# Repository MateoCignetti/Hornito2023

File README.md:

## Trabajo práctico final de Técnicas Digitales III y Medidas Electrónicas II. UTN FR San Francisco

En este repositorio se encuentran subidos todos los archivos relacionados al trabajo práctico final las materias Técnicas Digitales III y Medidas Electrónicas II. Contiene archivos de programación de los microcontroladores, esquemáticos del circuito y de pcb, y recursos varios.

## Autores

- [ ] Alesandria, Alejo
- [ ] Cignetti, Mateo
- [ ] Delfino, Ramiro
- [ ] Galliano, Ignacio
- [ ] Rinaudo, Facundo
- [ ] Rodriguez, Manuel

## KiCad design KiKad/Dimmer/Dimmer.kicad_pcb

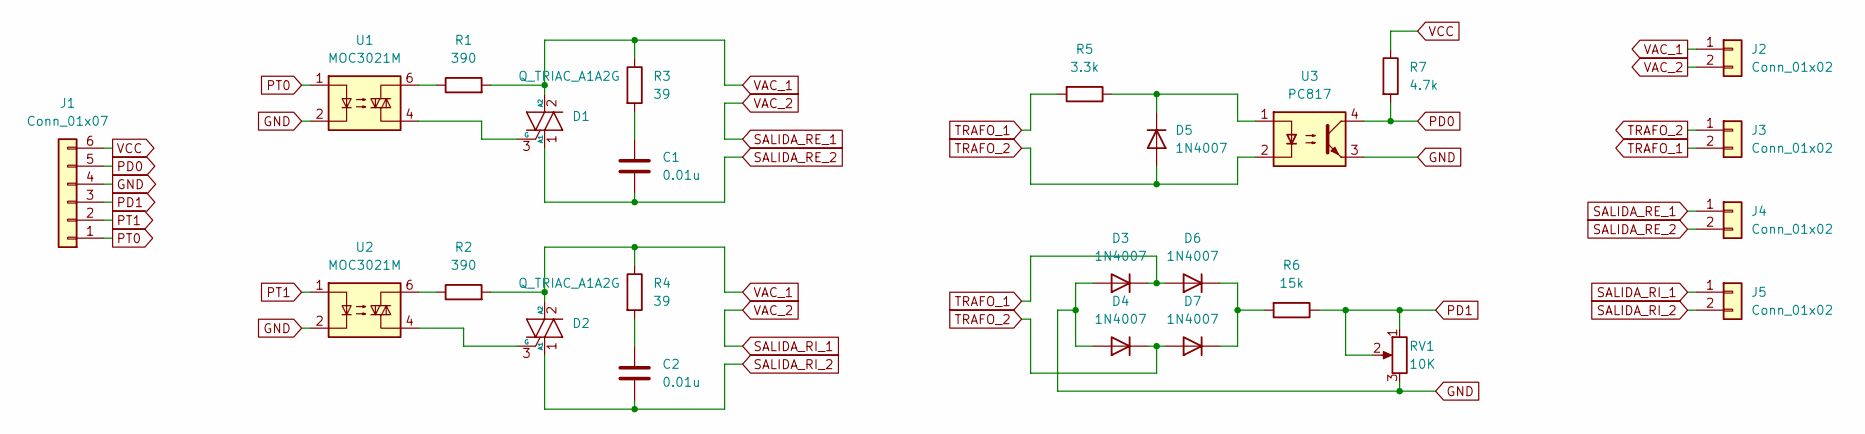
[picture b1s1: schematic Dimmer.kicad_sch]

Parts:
C1, C2: 0.01u; C_Axial_L5.1mm_D3.1mm_P10.00mm_Horizontal
D1, D2: Q_TRIAC_A1A2G; TO-220-3_Vertical
D3, D4, D5, D6, D7: 1N4007; D_DO-41_SOD81_P10.16mm_Horizontal
J1: Conn_01x07; PinHeader_1x06_P2.54mm_Vertical
J2, J3, J4, J5: Conn_01x02; TerminalBlock_bornier-2_P5.08mm
R1, R2: 390; R_Axial_DIN0207_L6.3mm_D2.5mm_P10.16mm_Horizontal
R3, R4: 39; R_Axial_DIN0207_L6.3mm_D2.5mm_P10.16mm_Horizontal
R5: 3.3k; R_Axial_DIN0207_L6.3mm_D2.5mm_P10.16mm_Horizontal
R6: 15k; R_Axial_DIN0207_L6.3mm_D2.5mm_P10.16mm_Horizontal
R7: 4.7k; R_Axial_DIN0207_L6.3mm_D2.5mm_P10.16mm_Horizontal
RV1: 10K; Potentiometer_Bourns_3296W_Vertical
U1, U2: MOC3021M; DIP-6_W7.62mm_LongPads
U3: PC817; DIP-4_W7.62mm_LongPads

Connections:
GND: D3.2 (A), D4.2 (A), J1.4, RV1.3, U1.2, U2.2, U3.3
unnamed: C1.1, R3.2
unnamed: C2.1, R4.2
unnamed: D1.3 (G), U1.4
unnamed: D2.3 (G), U2.4
unnamed: D5.1 (K), R5.1, U3.1
unnamed: D6.1 (K), D7.1 (K), R6.2
unnamed: R1.1, U1.6
unnamed: R2.1, U2.6
PD0: J1.5, R7.2, U3.4
PD1: J1.3, R6.1, RV1.1, RV1.2
PT0: J1.1, U1.1
PT1: J1.2, U2.1
SALIDA_RE_1: J2.2, J4.1, J5.1
SALIDA_RE_2: C1.2, D1.1 (A1), J4.2
SALIDA_RI_2: C2.2, D2.1 (A1), J5.2
TRAFO_1: D3.1 (K), D6.2 (A), J3.2, R5.2
TRAFO_2: D4.1 (K), D5.2 (A), D7.2 (A), J3.1, U3.2
VAC_1: D1.2 (A2), D2.2 (A2), J2.1, R1.2, R2.2, R3.1, R4.1
VCC: J1.6, R7.1

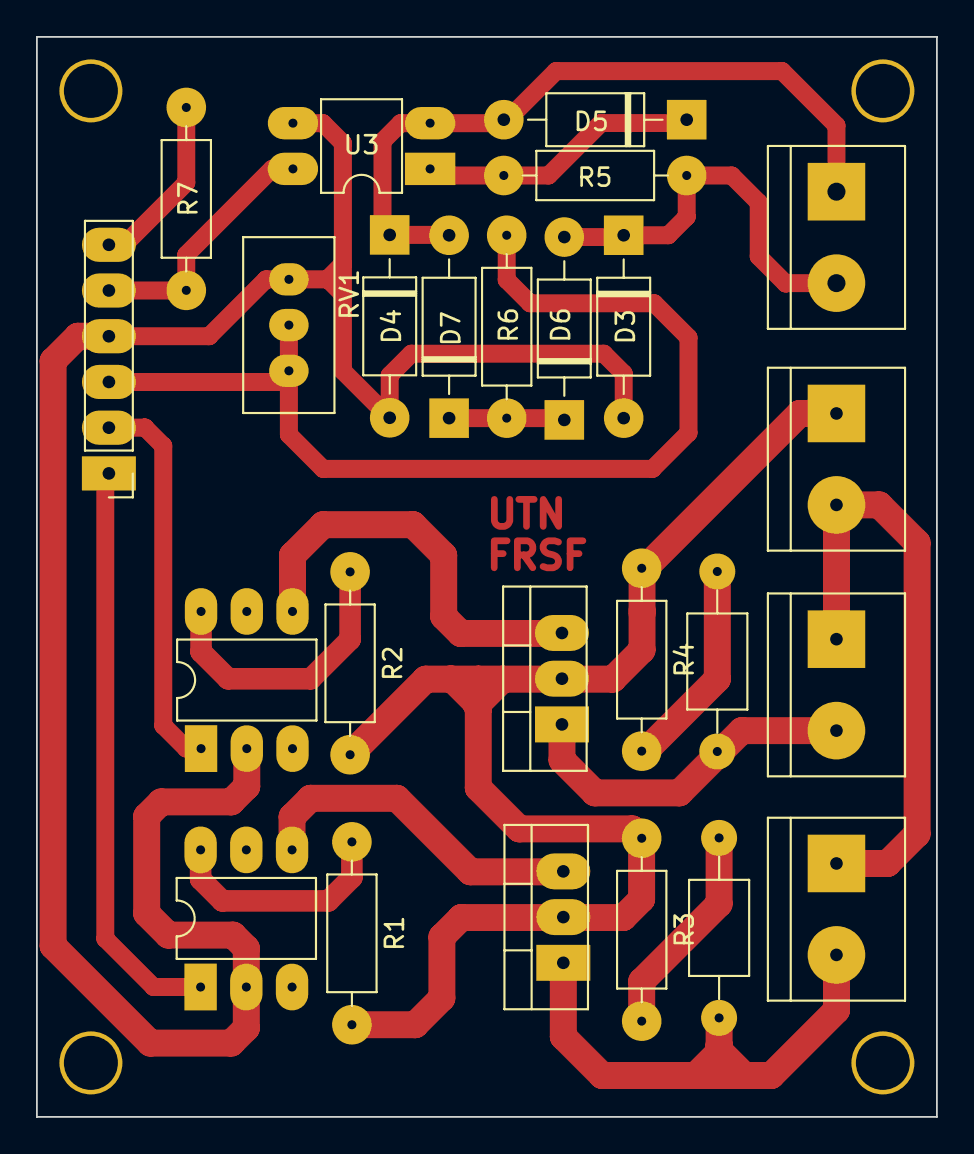
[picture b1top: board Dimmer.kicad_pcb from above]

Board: 2 copper layers, 50.0 x 60.0 mm, 25 parts (0 on the bottom side), 20 nets.

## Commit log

2023-05-18 Modificar gitignore
2023-05-18 Agregar programa test adc
2023-06-09 Agregar código test del dimmer
2023-06-13 Finalizar código de test de dimmer
2023-08-01 Agregar funcionalidad de medición de resistencia y dimmer mediante archivos .c y .h, no funciona todavía la funcionalidad del dimmer
2023-08-03 Solucionar funcionamiento del dimmer, agregar medición de temperatura con NTC
2023-09-01 Agregar test wifi y http webserver, realizado en conjunto con Manu
2023-09-18 Organizar repo y agregar recursos
2023-09-19 Agregar carpeta y diagrama de flujo de sistema de refrigeracion en conjunto con Facu
2023-09-19 Agregar test de tiempo
2023-09-25 Agregar idea del html, en conjunto con Manu
2023-09-26 Modificacion de diagrama de flujo y agregado de programa de control
2023-09-26 Probar filtro MAV para medicion de temperatura
2023-09-26 Modificar http-test para implementar carga de EPOCH, en conjunto con Manu
2023-09-29 Agregar pinout correcto, remover el otro
2023-09-29 Agregar código test de adc para plottear la señal de entrada al adc
2023-10-03 Solucionar redireccionamiento luego de presionar el botón
2023-10-03 Implementación de tabla con agregado de filas por html
2023-10-13 Diseño PCB Dimmer
2023-10-13 Fix #4
2023-10-13 Cambiar nombre de carpeta Código a Codigo para evitar problemas
2023-10-13 Agregar comentarios en http-test
2023-10-13 Rediseñar completamente el driver adc
2023-10-13 Agregar más comentarios a http-test
2023-10-18 Añadir recursos linealización de NTC
2023-10-18 Añadir informe anteproyecto
2023-10-20 Mover funcionalidad del ntc del adc.c/h a ntc.c/h
2023-10-21 Método rudimentario para agregar datos a la tabla de un ntc y tiempo actual
2023-10-24 Agregar código de prueba peltier
2023-10-24 Actualizar codigo peltier segun nueva libreria
2023-10-24 Agregar función de obtención de tensión de adc sin multisampling, arreglos varios y fix de #5
2023-10-27 Implementar #6
2023-10-29 Arreglar tarea de debugging con el nuevo driver, crear task.c/.h para manejar la creación de tareas de FreeRTOS
2023-10-30 Agregar versión inicial medición tensión rms
2023-11-03 Agregar hoja de datos del NTC de 100k
2023-11-03 Version final test-peltier
2023-11-03 Medidor de tensión RMS funcionando
2023-11-07 Agregar tarea para actualización de datos. Incluir botón de inicio
2023-11-07 Agregar sistema de control simple para potencia
2023-11-10 Subir espA con dimmer
2023-11-10 Agregar código vrms en fase, no funcional por lentitud de la tarea
2023-11-10 Agregar código vrms en fase, funcional
2023-11-10 Arreglar sistema de control de alejo, agregar mejoras en la interrupción
2023-11-10 Agregar botón de guardado y finalización
2023-11-10 Terminar sistema de control
2023-11-10 Implementar semáforo y tarea para cuando el webserver lo pida
2023-11-10 Agregar archivo excel
2023-11-13 Agregar webserver.c y sincronización con power.c
2023-11-13 Terminar sistema control, agregar Queue y semph
2023-11-13 Acomodar y comentar código de medición de potencia
2023-11-13 Arreglar fórmula de potencia
2023-11-13 Agregar envio steps a power.c
2023-11-14 Agregar sincronización para actualización de datos
2023-11-14 Agregar comunicación con tarea de sistema de control, modificaciones varias
2023-11-14 Corregir control system
2023-11-14 Actuallizar control_system.c
2023-11-14 Agregar comunicación entre tareas y mejora del sistema de control
2023-11-14 Corregir errores varios del sistema de control de placa fría
2023-11-14 Modificar Hornito-ESPA
2023-11-14 Modificar excel
2023-11-14 Cambiar imagen del pinout del devkit
2023-11-14 Corregir Hornito-ESPA
2023-11-14 Agregar monitor control_system.c
2023-11-14 Agregar versión inicial excel de tareas
2023-11-14 Agregar tarea monitoreo
2023-11-14 Arreglar creación de mutex y queues según existencia anterior
2023-11-14 Agregar sección critica en el timer y modificar delay de potencia
2023-11-14 Agregar tarea de monitoreo
2023-11-14 Modificar prioridades y núcleos de taras
2023-11-14 Agregar un ; y comentar sección crítica
2023-11-15 Agregar notas excel, modificaciones en prioridades y stack, no funcional el guardado en archivo y eliminación de tareas
2023-11-15 Agregar comentarios a power.c y corregir arreglo de muestras de float a int
2023-11-15 Agregar comentarios adc.h y adc.c
2023-11-15 Agregar comentarios
2023-11-15 Agregar comentarios dimmer.c y dimmer.h
2023-11-16 Agregar comentarios y especificar programas
2023-11-16 Agregar comentarios y descripcion de codigo
2023-11-16 Arreglar declaración de ISR de dimmer
2023-11-16 Invertir prioridad tarea dimmer y power
2023-11-16 Agregar comentarios control_system.c y .h
2023-11-16 Reducir tamaño de muestras de multisampling y aumentar delay entre medición
2023-11-16 Agregar codigo de creacion de semaforo y queue
2023-11-16 Agregar código de creación de semáforos y colas independiente de la creación de tareas en power.c y control_system.c
2023-11-16 Modificar prioridades tareas
2023-11-16 Aumentar stack size y mover creación de mutex al inicio de la creación de tareas
2023-11-16 Agregar tarea de monitoreo dimmer.c
2023-11-16 Agregar tarea de monitoreo power.c
2023-11-16 Agregar tarea de monitoreo control_system.c
2023-11-16 Agregar condicion tarea monitoreo
2023-11-16 Agregar define para la tarea de monitoreo de webserver
2023-11-16 Agregar codigo peltier a hornito-espA
2023-11-16 Modificar pins, delays y mejorar sistema de toma de mediciones con un semáforo
2023-11-16 Actualizar excel con datos actuales
2023-11-17 Arreglar control_system.c
2023-11-17 Mejorar delete tasks
2023-11-17 Arreglar control_system.c y webserver I/P
2023-11-21 Modificar control_system.c
2023-11-21 Modificacion sistema de control y tiempos
2023-11-22 Corregir toma de mutex al enviar los steps en control_system.c
2023-11-22 Modificar secuencia de liberación de semáforos
2023-11-22 Agregar mas mediciones al multisampling y modificar controlsystem
2023-11-22 Filtro MAV
2023-11-22 Modificaciones de alejo mav filter
2023-11-23 Terminar filtro MAV
2023-11-23 Corregir variables filtro MAV
2023-11-23 Mover ejemplos a carpeta aparte, modificar readme
2023-11-24 Prueba 23/11/23
2023-11-25 Subir informe
